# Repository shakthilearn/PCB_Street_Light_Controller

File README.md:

# Pcb_Project
PCB for a Automatic street light controller, which controls the AC street light by using a simple BJT Transistor BC547 and a LDR sensor with the switching control using a relay.

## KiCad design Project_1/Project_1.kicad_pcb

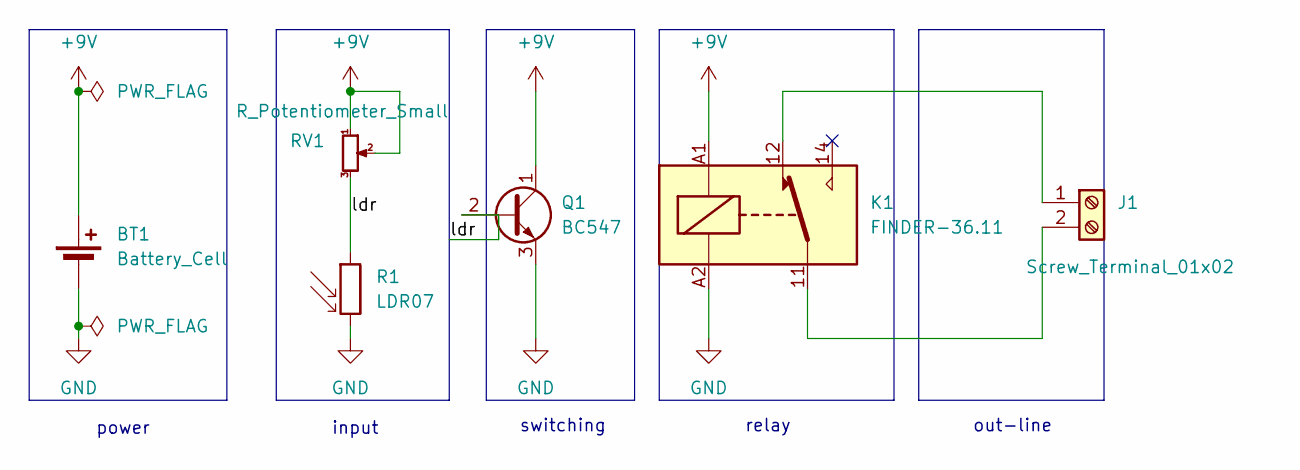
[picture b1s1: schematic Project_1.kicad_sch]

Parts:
BT1: Battery_Cell; BatteryHolder_Keystone_3001_1x12mm
J1: Screw_Terminal_01x02; TerminalBlock_MetzConnect_Type059_RT06302HBWC_1x02_P3.50mm_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
K1: FINDER-36.11; Relay_SPDT_Finder_36.11
Q1: BC547; TO-92_Inline
R1: LDR07; R_LDR_5.1x4.3mm_P3.4mm_Vertical
RV1: R_Potentiometer_Small; Potentiometer_ACP_CA9-V10_Vertical

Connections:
+9V: BT1.1 (+), K1.A1, Q1.1 (C), RV1.1, RV1.2
/ldr: Q1.2 (B), R1.1, RV1.3
GND: BT1.2 (-), K1.A2, Q1.3 (E), R1.2
unnamed: J1.1, K1.12
unnamed: J1.2, K1.11

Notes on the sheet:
input
relay
power
out-line
switching

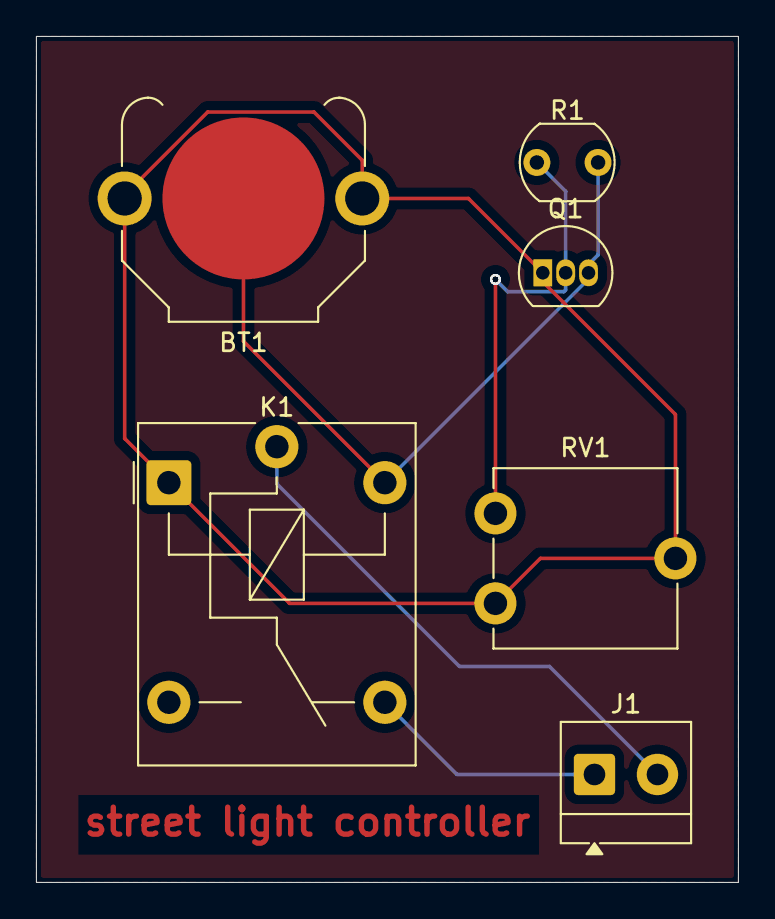
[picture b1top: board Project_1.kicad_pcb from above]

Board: 2 copper layers, 39.0 x 47.0 mm, 6 parts (0 on the bottom side), 5 nets.
